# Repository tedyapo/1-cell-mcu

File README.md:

# 1-cell-mcu
Experimental design for efficient single-cell (Alkaline/NiMH/LiFeS2) MCU power supply using MCP1624

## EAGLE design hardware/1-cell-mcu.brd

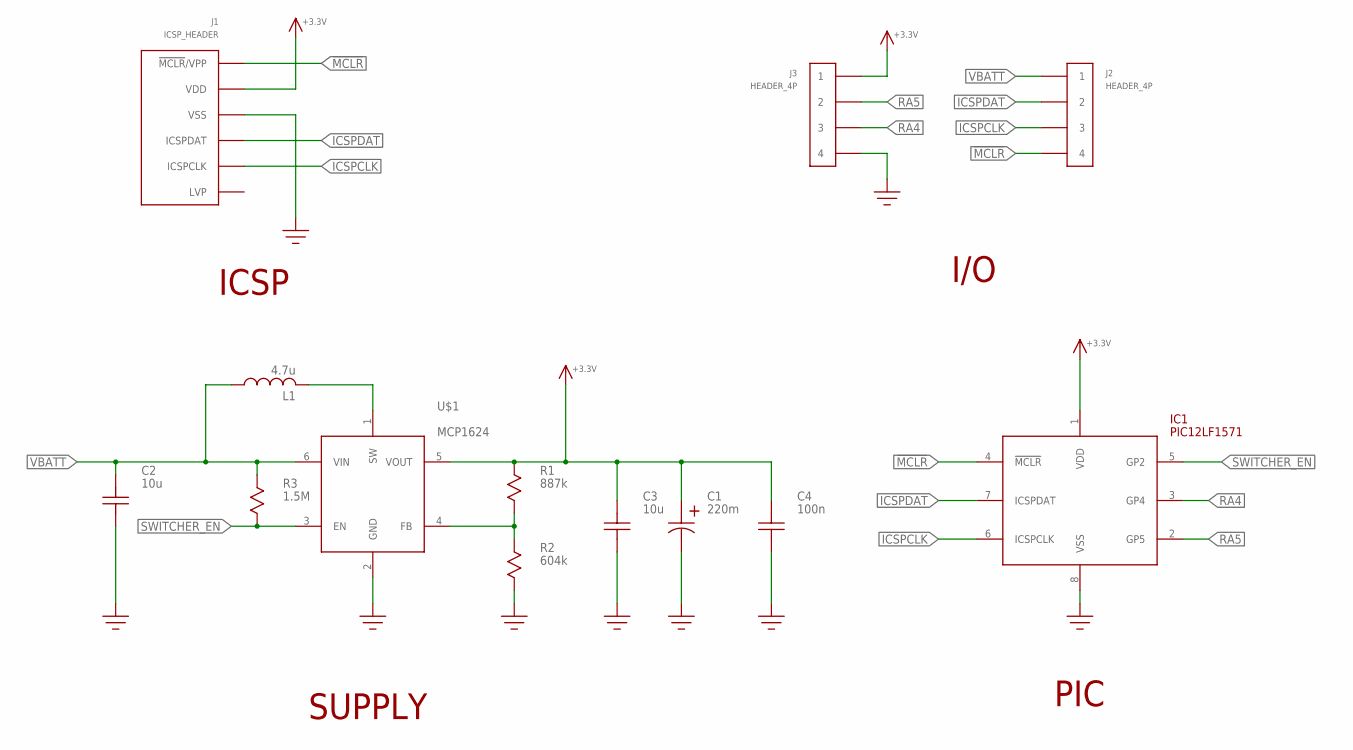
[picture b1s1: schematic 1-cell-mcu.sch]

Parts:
C1: 220m; ELNA_HL_SUPERCAP
C2, C3: 10u; 1206
C4: 100n; 0805
IC1: PIC12LF1571; SOIC8
J1: ICSP_HEADER; HEADER_6P
J2, J3: HEADER_4P
L1: 4.7u; 4040_INDUCTOR
R1: 887k; R0805
R2: 604k; R0805
R3: 1.5M; R0805
U$1: MCP1624; SOT23-6

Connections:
!MCLR!: IC1.4 (!MCLR!), J1.1 (!MCLR!/VPP), J2.4
+3.3V: C1.+, C3.P$2, C4.P$2, IC1.1 (VDD), J1.2 (VDD), J3.1, R1.P$1, U$1.5 (VOUT)
GND: C1.-, C2.P$1, C3.P$1, C4.P$1, IC1.8 (VSS), J1.3 (VSS), J3.4, R2.P$2, U$1.2 (GND)
ICSPCLK: IC1.6 (ICSPCLK), J1.5 (ICSPCLK), J2.3
ICSPDAT: IC1.7 (ICSPDAT), J1.4 (ICSPDAT), J2.2
unnamed: L1.P$2 (2), U$1.1 (SW)
unnamed: R1.P$2, R2.P$1, U$1.4 (FB)
RA4: IC1.3 (GP4), J3.3
RA5: IC1.2 (GP5), J3.2
SWITCHER_EN: IC1.5 (GP2), R3.P$2, U$1.3 (EN)
VBATT: C2.P$2, J2.1, L1.P$1 (1), R3.P$1, U$1.6 (VIN)

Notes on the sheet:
ICSP
I/O
SUPPLY
PIC

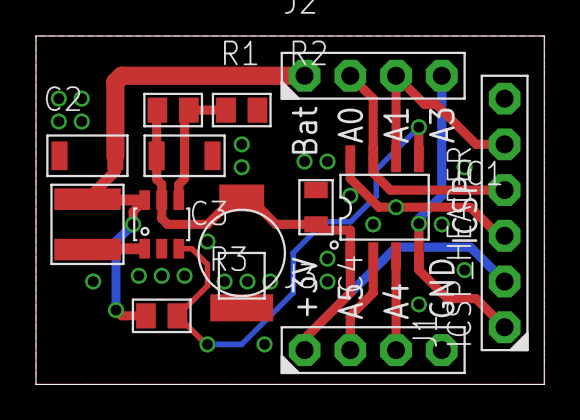
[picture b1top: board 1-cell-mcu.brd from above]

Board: 2 copper layers, 28.2 x 19.4 mm, 13 parts (0 on the bottom side), 11 nets.

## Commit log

2018-03-11 first checkin
2018-03-11 updated supercap value
